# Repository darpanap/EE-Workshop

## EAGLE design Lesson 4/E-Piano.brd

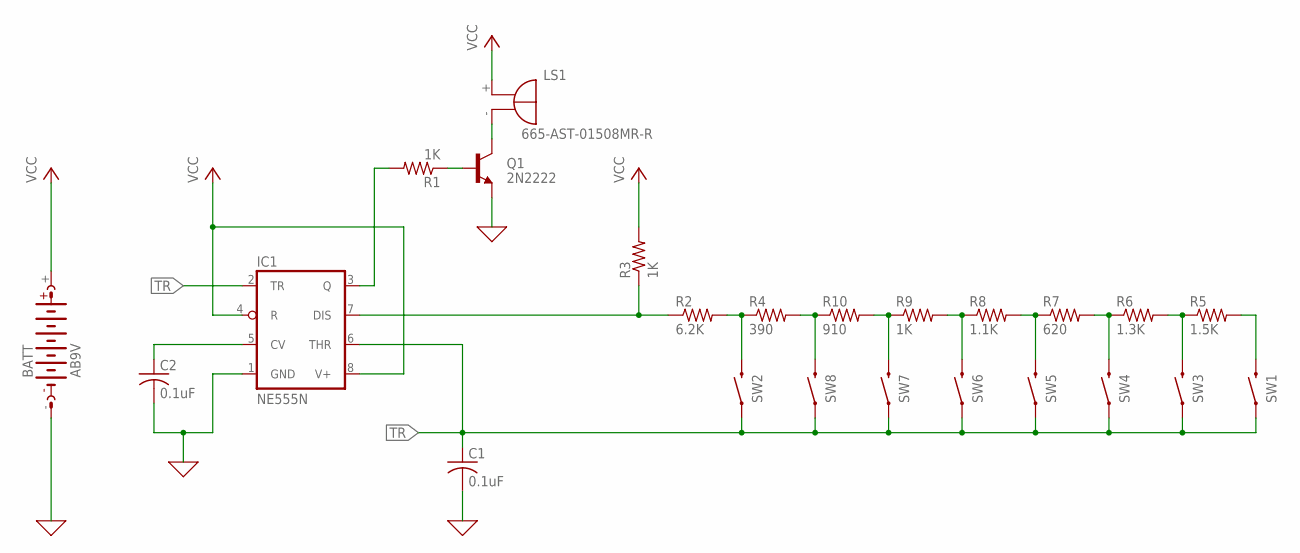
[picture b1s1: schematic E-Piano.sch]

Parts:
BATT: AB9V
C1, C2: 0.1uF; C025-025X050; MOUSER# 581-SR201C104KARTR1
IC1: NE555N; DIL08; MOUSER# 595-TLC555CP
LS1: F/HMB; MOUSER# 665-AST-01508MR-R
Q1: 2N2222; TO92-E1; MOUSER# 833-PN2222A-AP
R1, R3, R9: 1K; 0207/10; MOUSER# 660-MF1/4DCT26A1001F
R2: 6.2K; 0207/10; MOUSER# 603-MFR-25FRF52-6K2
R4: 390; 0207/10; MOUSER# 603-MFR-25FTE52-390R
R5: 1.5K; 0207/10; MOUSER# 603-MFR-25FBF52-1K5
R6: 1.3K; 0207/10; MOUSER# 603-MFR-25FBF52-1K3
R7: 620; 0207/10; MOUSER# 603-MFR-25FBF52-620R
R8: 1.1K; 0207/10; MOUSER# 603-MFR-25FBF52-1K1
R10: 910; 0207/10; MOUSER# 603-MFR-25FRF52-910R
SW1, SW2, SW3, SW4, SW5, SW6, SW7, SW8: MOMENTARY-SWITCH-SPST-PTH-6.0MM; TACTILE_SWITCH_PTH_6.0MM; MOUSER# 653-B3F-1000

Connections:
0: BATT.-, C1.2, C2.2, IC1.1 (GND)
GND: Q1.3 (E)
unnamed: R2.2, R4.1, SW2.3 (2)
unnamed: IC1.7 (DIS), R2.1, R3.1
unnamed: R4.2, R10.1, SW8.3 (2)
unnamed: R9.1, R10.2, SW7.3 (2)
unnamed: R8.1, R9.2, SW6.3 (2)
unnamed: R7.1, R8.2, SW5.3 (2)
unnamed: R6.1, R7.2, SW4.3 (2)
unnamed: R5.1, R6.2, SW3.3 (2)
unnamed: R5.2, SW1.3 (2)
unnamed: IC1.3 (Q), R1.2
unnamed: C2.1, IC1.5 (CV)
unnamed: LS1.-, Q1.1 (C)
unnamed: Q1.2 (B), R1.1
TR: C1.1, IC1.2 (TR), IC1.6 (THR), SW1.1, SW2.1, SW3.1, SW4.1, SW5.1, SW6.1, SW7.1, SW8.1
VCC: BATT.+, IC1.4 (R), IC1.8 (V+), LS1.+, R3.2

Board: 2 copper layers, 24 parts (0 on the bottom side), 16 nets, no tracks yet.

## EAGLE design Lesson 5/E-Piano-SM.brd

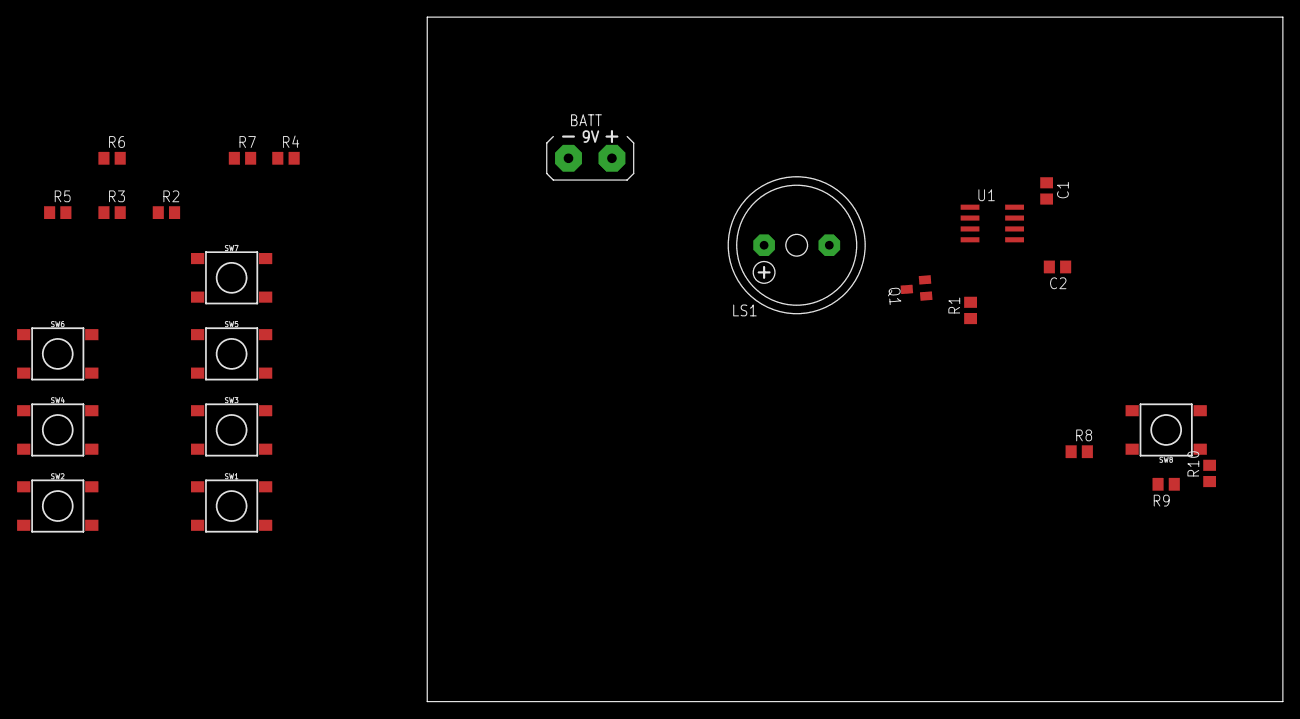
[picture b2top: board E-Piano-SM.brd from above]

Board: 2 copper layers, 100.0 x 80.0 mm, 24 parts (0 on the bottom side), 16 nets, no tracks yet.

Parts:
BATT: AB9V
C1, C2: 0.1uF; C0805
LS1: F/HMB
Q1: BCW66; SOT23-BEC
R1, R6, R10: 1K; R0805
R2: 1.5K; R0805
R3: 1.3K; R0805
R4: 620; R0805
R5: 1.1K; R0805
R7: 910; R0805
R8: 390; R0805
R9: 6.2K; R0805
SW1, SW2, SW3, SW4, SW5, SW6, SW7, SW8: MOMENTARY-SWITCH-SPST-SMD-6.2MM-TALL; TACTILE_SWITCH_SMD_6.2MM_TALL
U1: NE555D; SO08

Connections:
0: BATT.-, C1.2, C2.2, Q1.E, U1.1
unnamed: R8.2, R9.2, SW8.B2
unnamed: R9.1, R10.1, U1.7
unnamed: R2.1, SW1.B2
unnamed: R7.2, R8.1, SW7.B2
unnamed: R6.2, R7.1, SW6.B2
unnamed: R5.2, R6.1, SW5.B2
unnamed: R4.2, R5.1, SW4.B2
unnamed: R3.2, R4.1, SW3.B2
unnamed: R2.2, R3.1, SW2.B2
unnamed: R1.2, U1.3
unnamed: C1.1, U1.5
unnamed: LS1.-, Q1.C
unnamed: Q1.B, R1.1
TR: C2.1, SW1.A2, SW2.A2, SW3.A2, SW4.A2, SW5.A2, SW6.A2, SW7.A2, SW8.A2, U1.2, U1.6
VCC: BATT.+, LS1.+, R10.2, U1.4, U1.8

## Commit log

2019-05-15 Piano
2019-05-18 Schematic
2019-05-22 05/21 Piano Layout

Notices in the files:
parts and their libraries:
SparkFun-Switches: Licensing: Creative Commons ShareAlike 4.0 International - https://creativecommons.org/licenses/by-sa/4.0
